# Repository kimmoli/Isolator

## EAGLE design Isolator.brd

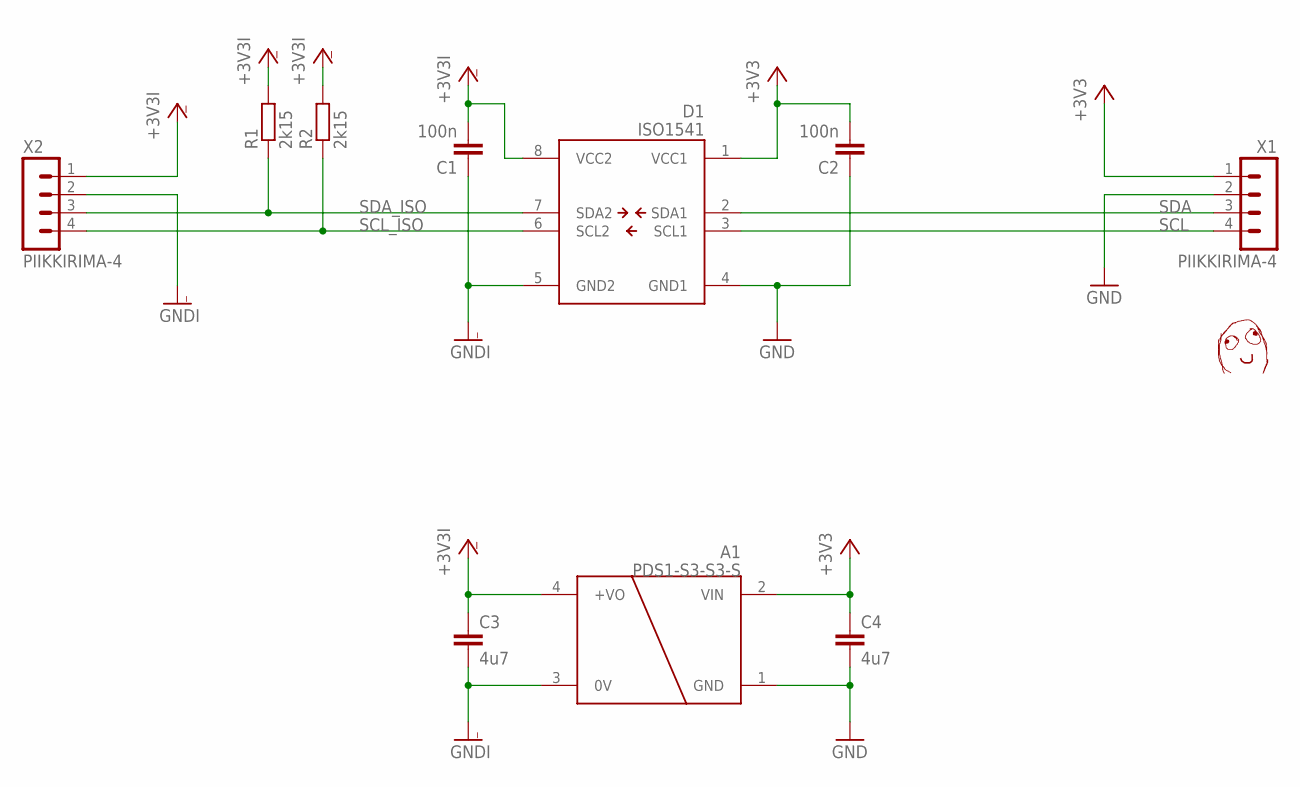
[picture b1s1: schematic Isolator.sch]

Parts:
A1: PDS1-S3-S3-S; DCDC_SIP4
C1, C2: 100n; C0603
C3, C4: 4u7; C0805
D1: ISO1541; SOIC8-N_MC
R1, R2: 2k15; R0603
U$1: DAFUG
X1, X2: PIIKKIRIMA-4

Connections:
+3V3: A1.2 (VIN), C2.2, C4.1, D1.1 (VCC1), X1.1
+3V3I: A1.4 (+VO), C1.2, C3.1, D1.8 (VCC2), R1.2, R2.2, X2.1
GND: A1.1 (GND), C2.1, C4.2, D1.4 (GND1), X1.2
GNDI: A1.3 (0V), C1.1, C3.2, D1.5 (GND2), X2.2
SCL: D1.3 (SCL1), X1.4
SCL_ISO: D1.6 (SCL2), R2.1, X2.4
SDA: D1.2 (SDA1), X1.3
SDA_ISO: D1.7 (SDA2), R1.1, X2.3

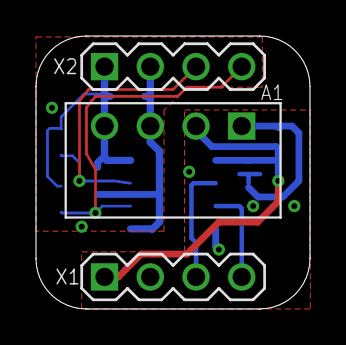
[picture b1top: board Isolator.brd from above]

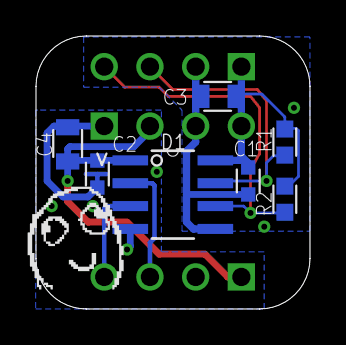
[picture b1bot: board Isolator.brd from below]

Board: 2 copper layers, 15.2 x 15.2 mm, 11 parts (8 on the bottom side), 8 nets.
